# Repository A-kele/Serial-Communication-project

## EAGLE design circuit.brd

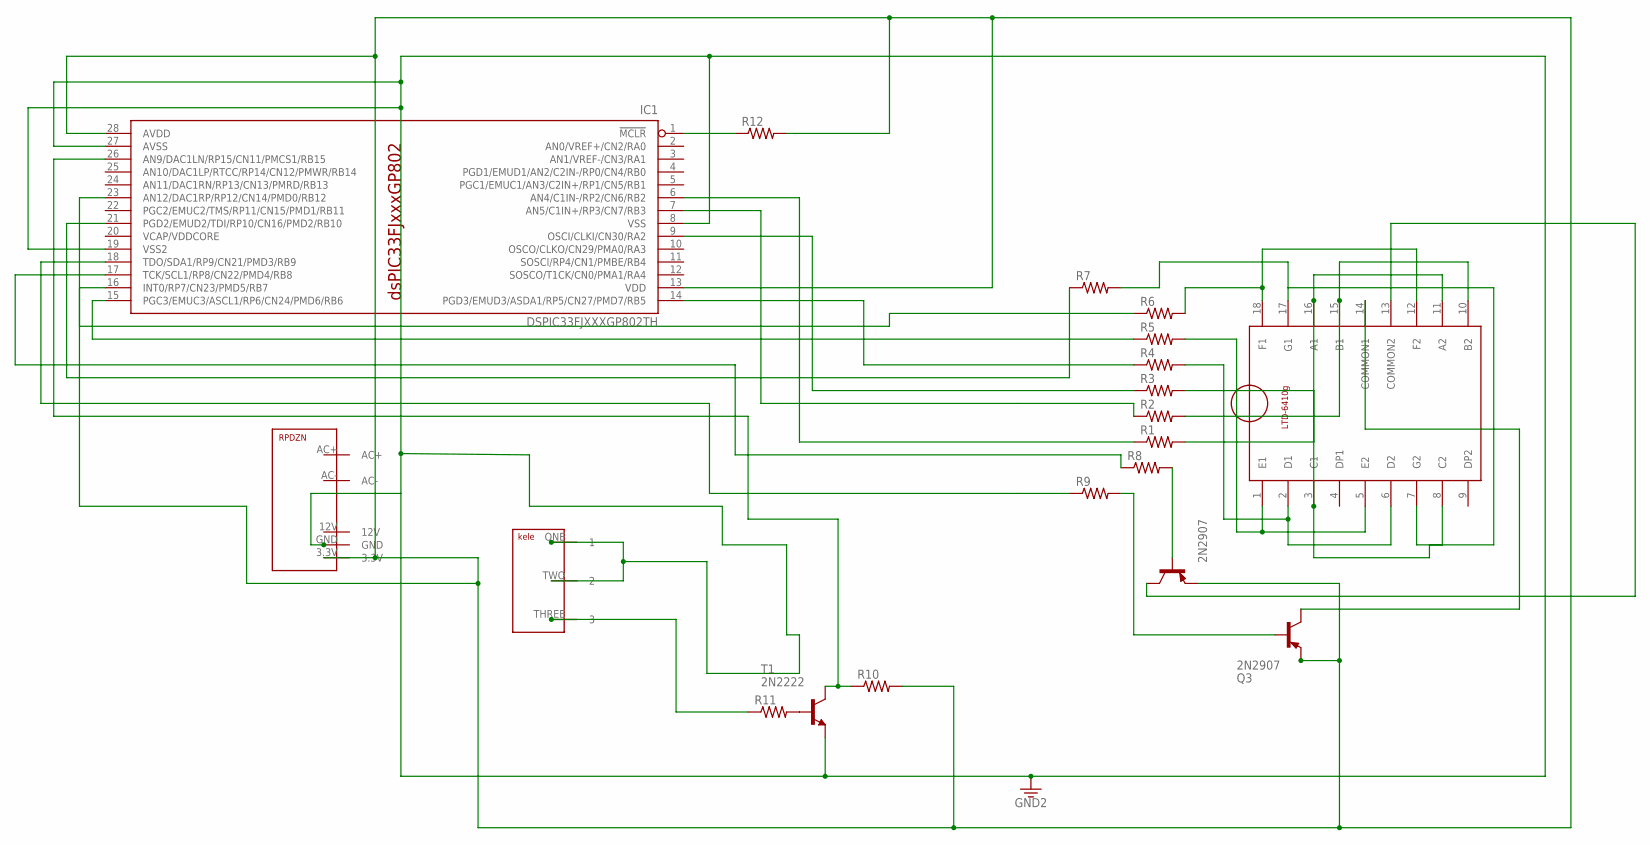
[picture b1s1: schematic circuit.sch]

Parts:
IC1: DSPIC33FJXXXGP802TH; DIL28-3
Q1, Q3: 2N2907; TO92-EBC-OVAL
R1, R2, R3, R4, R5, R6, R7, R8, R9, R10, R11, R12: R-US_0207/9; 0207/9
T1: 2N2222; TO92-EBC-OVAL
U$1: TERMINALTHROUGH-HOLE; TERMINAL
U$2: RODZN_AC-DC(3.3V)THROUGH-HOLE; RODZN_AC-DC(3.3V)
U$3: LIB-2THROUGH_HOLE; LIB-2

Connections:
GND: IC1.8 (VSS), IC1.19 (VSS2), IC1.27 (AVSS), T1.E, U$1.ONE (1), U$1.TWO (2), U$2.GND
unnamed: R1.2, U$3.11 (A2), U$3.16 (A1)
unnamed: R5.2, U$3.1 (E1), U$3.5 (E2)
unnamed: R3.2, U$3.3 (C1), U$3.8 (C2)
unnamed: R4.2, U$3.2 (D1), U$3.6 (D2)
unnamed: R7.2, U$3.7 (G2), U$3.17 (G1)
unnamed: R2.2, U$3.10 (B2), U$3.15 (B1)
unnamed: R6.2, U$3.12 (F2), U$3.18 (F1)
unnamed: IC1.6 (AN4/C1IN-/RP2/CN6/RB2), R1.1
unnamed: Q1.C, U$3.13 (COMMON2)
unnamed: Q3.B, R9.2
unnamed: Q1.B, R8.2
unnamed: IC1.1 (!MCLR), R12.1
unnamed: IC1.9 (OSCI/CLKI/CN30/RA2), R3.1
unnamed: IC1.13 (VDD), IC1.23 (AN12/DAC1RP/RP12/CN14/PMD0/RB12), IC1.28 (AVDD), Q1.E, Q3.E, R10.2, R12.2, U$2.3.3V
unnamed: IC1.14 (PGD3/EMUD3/ASDA1/RP5/CN27/PMD7/RB5), R4.1
unnamed: IC1.7 (AN5/C1IN+/RP3/CN7/RB3), R2.1
unnamed: IC1.15 (PGC3/EMUC3/ASCL1/RP6/CN24/PMD6/RB6), R5.1
unnamed: IC1.26 (AN9/DAC1LN/RP15/CN11/PMCS1/RB15), R10.1, T1.C
unnamed: IC1.16 (INT0/RP7/CN23/PMD5/RB7), R6.1
unnamed: IC1.21 (PGD2/EMUD2/TDI/RP10/CN16/PMD2/RB10), R7.1
unnamed: IC1.17 (TCK/SCL1/RP8/CN22/PMD4/RB8), R8.1
unnamed: R11.2, T1.B
unnamed: IC1.18 (TDO/SDA1/RP9/CN21/PMD3/RB9), R9.1
unnamed: Q3.C, U$3.14 (COMMON1)
unnamed: R11.1, U$1.THREE (3)
VCAP/VDDCORE: IC1.20 (VCAP/VDDCORE)

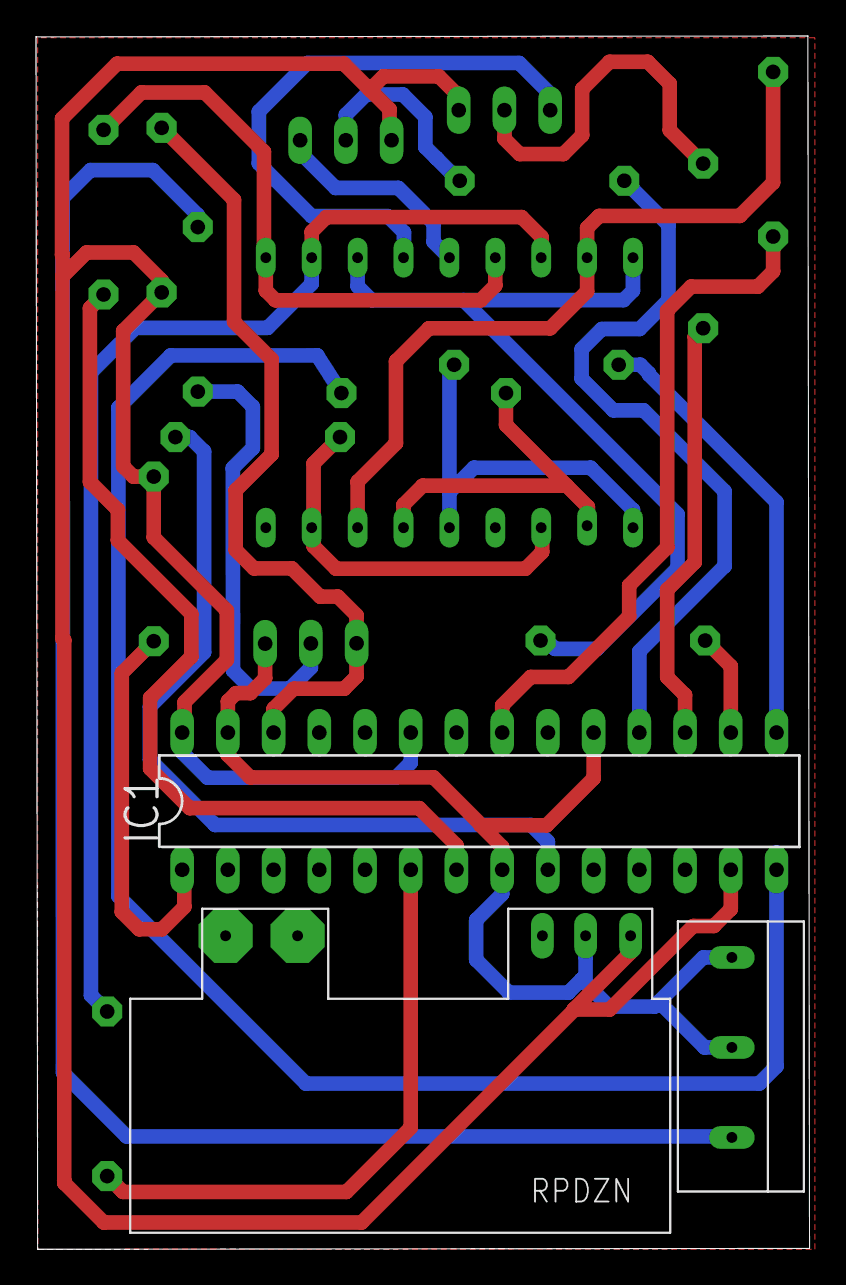
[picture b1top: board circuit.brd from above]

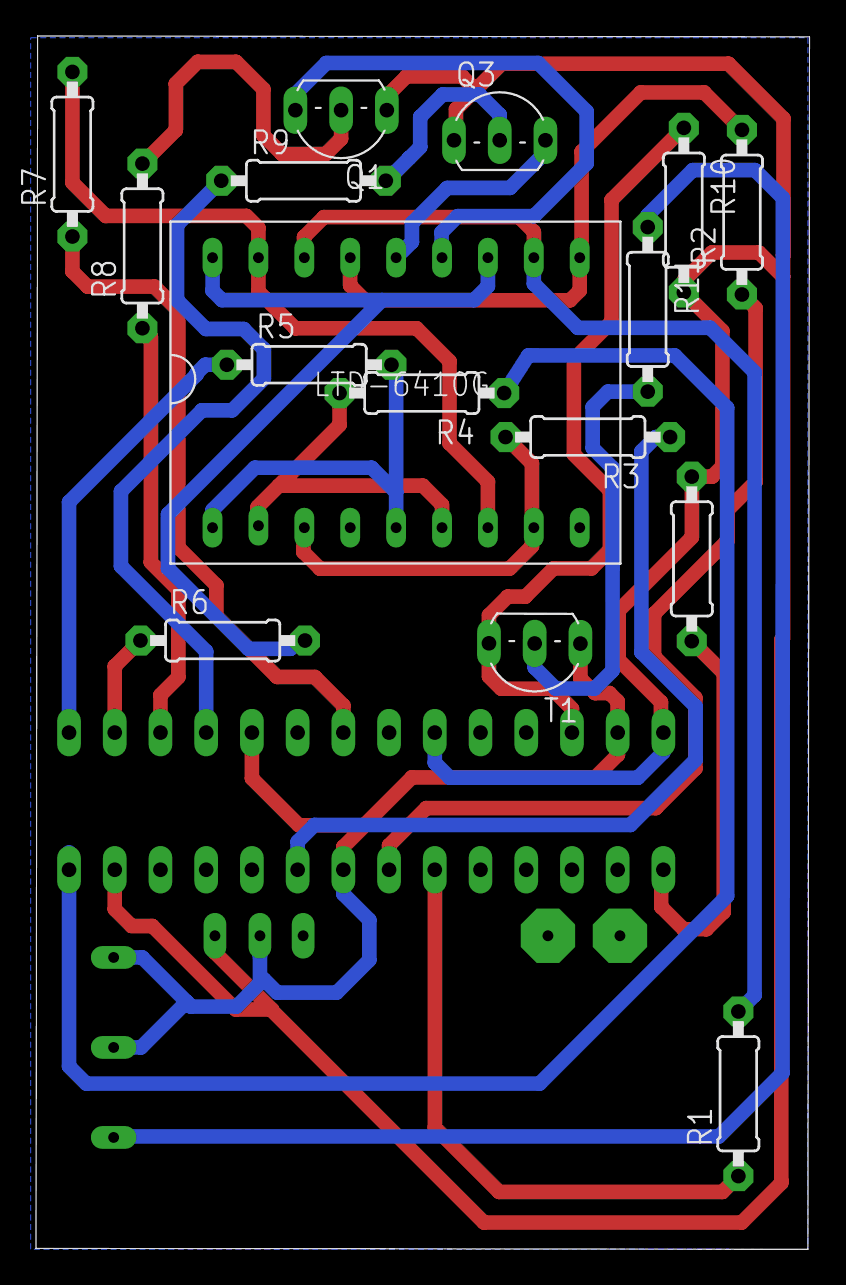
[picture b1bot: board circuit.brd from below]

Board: 2 copper layers, 43.0 x 67.4 mm, 19 parts (16 on the bottom side), 26 nets.

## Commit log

2023-05-29 Add files via upload
    Eagle files

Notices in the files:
parts and their libraries:
SparkFun-PowerSymbols: Licensing: Creative Commons ShareAlike 4.0 International - https://creativecommons.org/licenses/by-sa/4.0
